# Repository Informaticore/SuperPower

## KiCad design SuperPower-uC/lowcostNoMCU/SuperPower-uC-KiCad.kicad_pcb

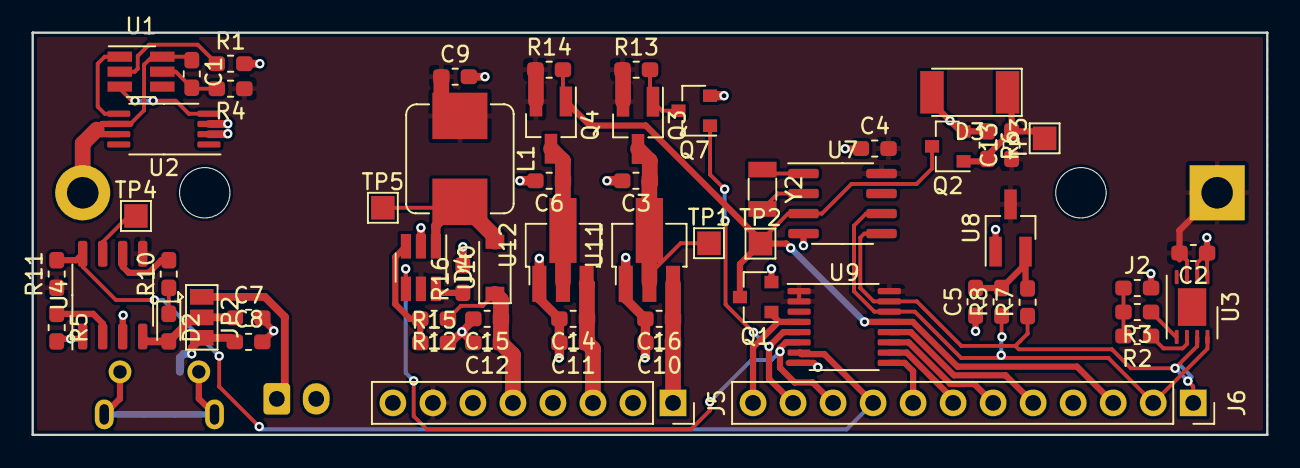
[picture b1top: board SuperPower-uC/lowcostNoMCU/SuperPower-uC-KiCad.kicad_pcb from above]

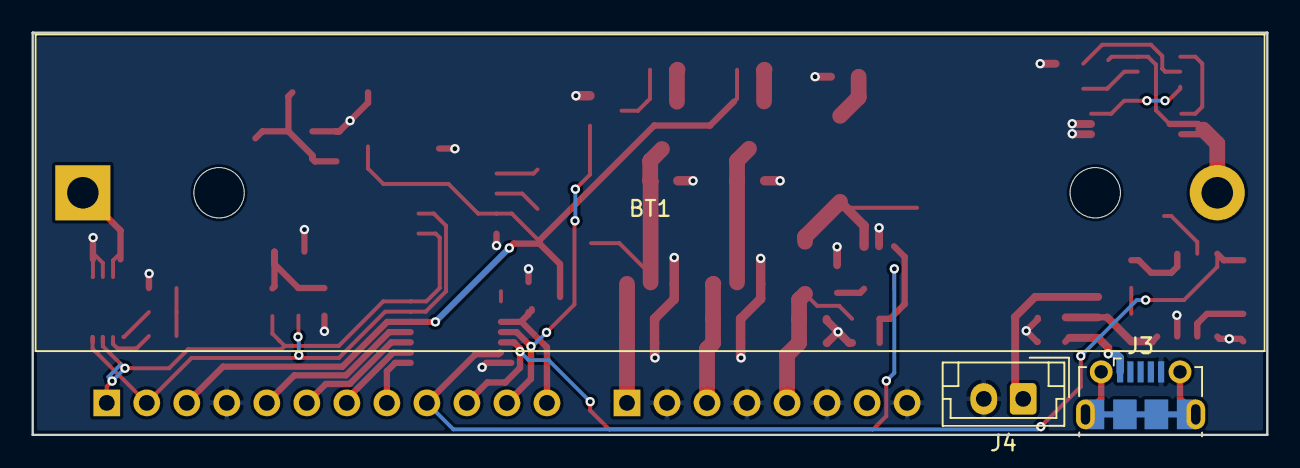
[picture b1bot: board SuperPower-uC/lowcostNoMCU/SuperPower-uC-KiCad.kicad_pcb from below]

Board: 2 copper layers, 78.4 x 25.5 mm, 63 parts (3 on the bottom side), 41 nets.

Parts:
BT1: Battery_Cell; BatteryHolder_MPD_BH-18650-PC2
C1, C2, C3, C4, C5, C6: 0.1µF; C_0603_1608Metric_Pad1.05x0.95mm_HandSolder
C7, C8, C9, C10, C11, C12: 1µF; C_0603_1608Metric_Pad1.05x0.95mm_HandSolder
C13, C14, C15, C16: 10µF; C_0603_1608Metric_Pad1.05x0.95mm_HandSolder
D2: LED; LED_0603_1608Metric_Pad1.05x0.95mm_HandSolder
D3: SM4007; D_MELF
D4: D_Schottky; D_SOD-123
J2: Thermistor; R_0603_1608Metric_Pad1.05x0.95mm_HandSolder
J3: USB_B_Micro; USB_Micro-B_Molex-105017-0001
J4: Solar in; JST_EH_B2B-EH-A_1x02_P2.50mm_Vertical
J5: Conn_01x08_Female; PinSocket_1x08_P2.54mm_Vertical
J6: Conn_01x12_Female; PinSocket_1x12_P2.54mm_Vertical
JP2: CHRG_Jumper; SolderJumper-3_P1.3mm_Open_Pad1.0x1.5mm
L1: 3.3u; L_Bourns_SRP7028A_7.3x6.6mm
Q1, Q2, Q7: 2N7002; SOT-23
Q3, Q4: AO3401A; SOT-23_Handsoldering
R1, R10: 1k; R_0603_1608Metric_Pad1.05x0.95mm_HandSolder
R2, R4: 100; R_0603_1608Metric_Pad1.05x0.95mm_HandSolder
R3, R7, R8: 10k; R_0603_1608Metric_Pad1.05x0.95mm_HandSolder
R5: 1.8k; R_0603_1608Metric_Pad1.05x0.95mm_HandSolder
R6: 1M; R_0603_1608Metric_Pad1.05x0.95mm_HandSolder
R11, R12, R13, R14: 180k; R_0603_1608Metric_Pad1.05x0.95mm_HandSolder
R15, R16: 22k; R_0603_1608Metric_Pad1.05x0.95mm_HandSolder
TP1, TP2, TP3, TP4, TP5: TestPoint; TestPoint_Pad_1.5x1.5mm
U1: FS312F-G; SOT-23-6_Handsoldering
U2: FS8205A; TSSOP-8_4.4x3mm_P0.65mm
U3: LC709203FQH; WDFN-8-1EP_4x3mm_P0.65mm_EP2.4x1.8mm
U4: TP4056; SOP-8_3.9x4.9mm_P1.27mm
U7: PCF8563T; SOIC-8_3.9x4.9mm_P1.27mm
U8: XC6206P332MR; SOT-23_Handsoldering
U9: TCA6408A; TSSOP-16_4.4x5mm_P0.65mm
U10: FP6291LR; SOT-23-6_Handsoldering
U11, U12: ME6210A33P; SOT-89-3_Handsoldering
Y2: 32.768KHz; Crystal_SMD_3215-2Pin_3.2x1.5mm

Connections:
/Battery Module/VBAT: BT1.1, C2.2, C4.2, C9.1, C13.1, J5.7, L1.1, Q3.2, Q4.2, R4.1, R11.1, R13.1, R14.1, U3.3, U4.5, U7.8, U8.3, U9.1, U9.2, U9.16, U10.5
/Charging Module/CHARGE-DISABLE: J6.9, R11.2, U4.8, U9.7
/Charging Module/INT: J6.3, Q1.3, Q2.3, Q4.1, R14.2, TP2.1, U7.3, U9.13
/Charging Module/SCL: J6.2, R8.1, U3.8, U7.6, U9.14
/Charging Module/SDA: J6.1, R7.1, U3.7, U7.5, U9.15
/Charging Module/STDBY: R10.2, U4.6
/Charging Module/VBUS: C8.1, J3.1, JP2.3
/Charging Module/VCHARGE: C7.1, D2.2, JP2.2, U4.4
/RTC and Cut-Off Module/3v3V_EN: J6.11, Q7.1, U9.5
/RTC and Cut-Off Module/3v3_MCU: C11.1, C14.1, J5.3, U12.3
/RTC and Cut-Off Module/5V_EN: J6.10, U9.6, U10.4
/RTC and Cut-Off Module/IO4: J6.8, U9.9
/RTC and Cut-Off Module/IO5: J6.7, U9.10
/RTC and Cut-Off Module/IO6: J6.6, U9.11
/RTC and Cut-Off Module/IO7: J6.5, U9.12
/RTC and Cut-Off Module/IO_INT: J6.12, Q1.1, U9.4
/RTC and Cut-Off Module/V_I2C: C5.2, R7.2, R8.2, U8.2
/Regulator Module/3v3: C10.1, C16.1, J5.1, U11.3
/Regulator Module/5V: C12.1, C15.1, D4.1, J5.5, R12.1
GND: C2.1, C3.2, C4.1, C5.1, C6.2, C7.2, C8.2, C9.2, C10.2, C11.2, C12.2, C14.2, C15.2, C16.2, D3.2, J2.2, J3.5, J4.2, J5.2, J5.4, J5.6, J5.8, J6.4, Q1.2, Q2.2, Q7.2, R1.2, R5.2, R6.1, R15.2, R16.2, U2.2, U2.3, U3.1, U3.2, U4.1, U4.3, U7.4, U8.1, U9.8, U10.2, U11.1, U12.1
unnamed: BT1.2, C1.2, U1.6, U2.6, U2.7
unnamed: C1.1, R4.2, U1.5
unnamed: C3.1, Q3.3, TP1.1, U11.2
unnamed: C6.1, Q4.3, U12.2
unnamed: C13.2, D3.1, Q2.1, R6.2, TP3.1
unnamed: D2.1, R10.1
unnamed: D4.2, L1.2, TP5.1, U10.1
unnamed: J2.1, R2.2, R3.2
unnamed: J4.1, JP2.1
unnamed: Q3.1, Q7.3, R13.2
unnamed: R1.1, U1.2
unnamed: R2.1, U3.6
unnamed: R3.1, U3.5
unnamed: R5.1, U4.2
unnamed: R12.2, R15.1, U10.3
unnamed: R16.1, U10.6
unnamed: TP4.1, U4.7
unnamed: U1.1, U2.5
unnamed: U1.3, U2.4
unnamed: U7.1, Y2.2
unnamed: U7.2, Y2.1

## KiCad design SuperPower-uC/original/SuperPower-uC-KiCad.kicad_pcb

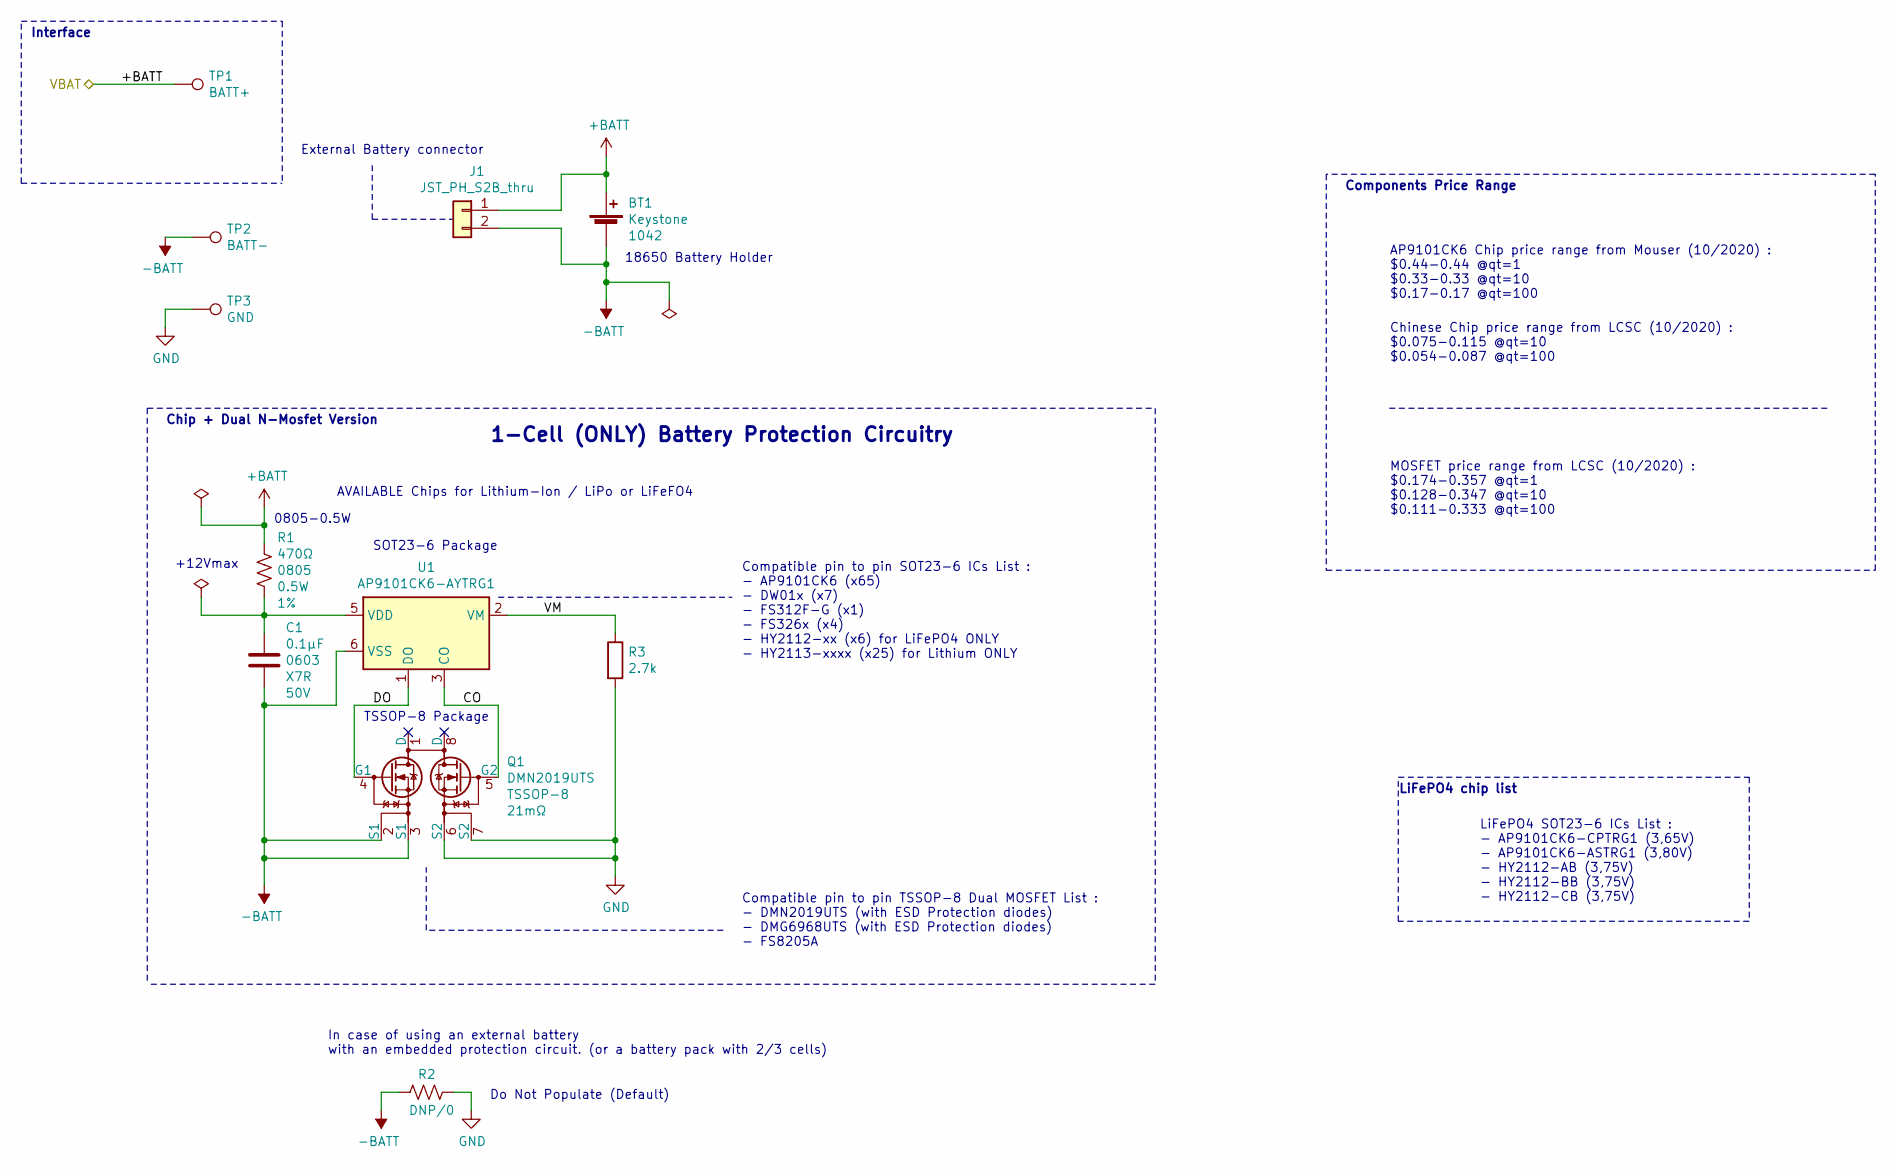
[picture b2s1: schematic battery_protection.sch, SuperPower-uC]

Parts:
BT1: Battery_Cell_Holder_18650_SMT_1042; BatteryHolder_Keystone_1042_1x18650; Farnell_ref ?
C1: CC0603JRX7R9BB104; C_0603_1608Metric; Farnell_ref 3369214
J1: JST_PH_S2B_thru; JST_PH_S2B-PH-K_1x02_P2.00mm_Horizontal; Farnell_ref 9491902
Q1: DMN2019UTS; TSSOP-8_4.4x3mm_P0.65mm; Farnell_check_date 2020-12-05
R1: ERJ-P06F4700V; R_0805_2012Metric; Farnell_check_date 2020-12-17
R2: DNP/0; R_0603_1608Metric
R3: 2.7k; R_0603_1608Metric
TP1: BATT+; TestPoint_Pad_D1.0mm
TP2: BATT-; TestPoint_Pad_D1.0mm
TP3: GND; TestPoint_Pad_D1.0mm
U1: AP9101CK6-AYTRG1; SOT-23-6; Farnell_check_date 2020-11-28

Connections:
+BATT: BT1.1 (+), J1.1, R1.1, TP1.1; also elsewhere on the board
-BATT: BT1.2 (-), C1.2, J1.2, Q1.2 (S1), Q1.3 (S1), R2.2, TP2.1, U1.6 (VSS)
/Battery Module/CO: Q1.5 (G2), U1.3 (CO)
/Battery Module/DO: Q1.4 (G1), U1.1 (DO)
/Battery Module/VM: R3.1, U1.2 (VM)
GND: Q1.6 (S2), Q1.7 (S2), R2.1, R3.2, TP3.1; also elsewhere on the board
unnamed: C1.1, R1.2, U1.5 (VDD)

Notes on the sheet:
SOT23-6 Package
TSSOP-8 Package
Compatible pin to pin SOT23-6 ICs List : - AP9101CK6 (x65) - DW01x (x7) - FS312F-G (x1) - FS326x (x4) - HY2112-xx (x6) for LiFePO4 ONLY - HY2113-xxxx (x25) for Lithium ONLY
AVAILABLE Chips for Lithium-Ion / LiPo or LiFeFO4
AP9101CK6 Chip price range from Mouser (10/2020) : $0.44-0.44 @qt=1 $0.33-0.33 @qt=10 $0.17-0.17 @qt=100
Compatible pin to pin TSSOP-8 Dual MOSFET List : - DMN2019UTS (with ESD Protection diodes) - DMG6968UTS (with ESD Protection diodes) - FS8205A
MOSFET price range from LCSC (10/2020) : $0.174-0.357 @qt=1 $0.128-0.347 @qt=10 $0.111-0.333 @qt=100
LiFePO4 SOT23-6 ICs List : - AP9101CK6-CPTRG1 (3,65V) - AP9101CK6-ASTRG1 (3,80V) - HY2112-AB (3,75V) - HY2112-BB (3,75V) - HY2112-CB (3,75V)
Chinese Chip price range from LCSC (10/2020) : $0.075-0.115 @qt=10 $0.054-0.087 @qt=100
Chip + Dual N-Mosfet Version
LiFePO4 chip list
In case of using an external battery with an embedded protection circuit. (or a battery pack with 2/3 cells)
External Battery connector
Interface
Components Price Range
18650 Battery Holder
1-Cell (ONLY) Battery Protection Circuitry
+12Vmax
Do Not Populate (Default)
0805-0.5W

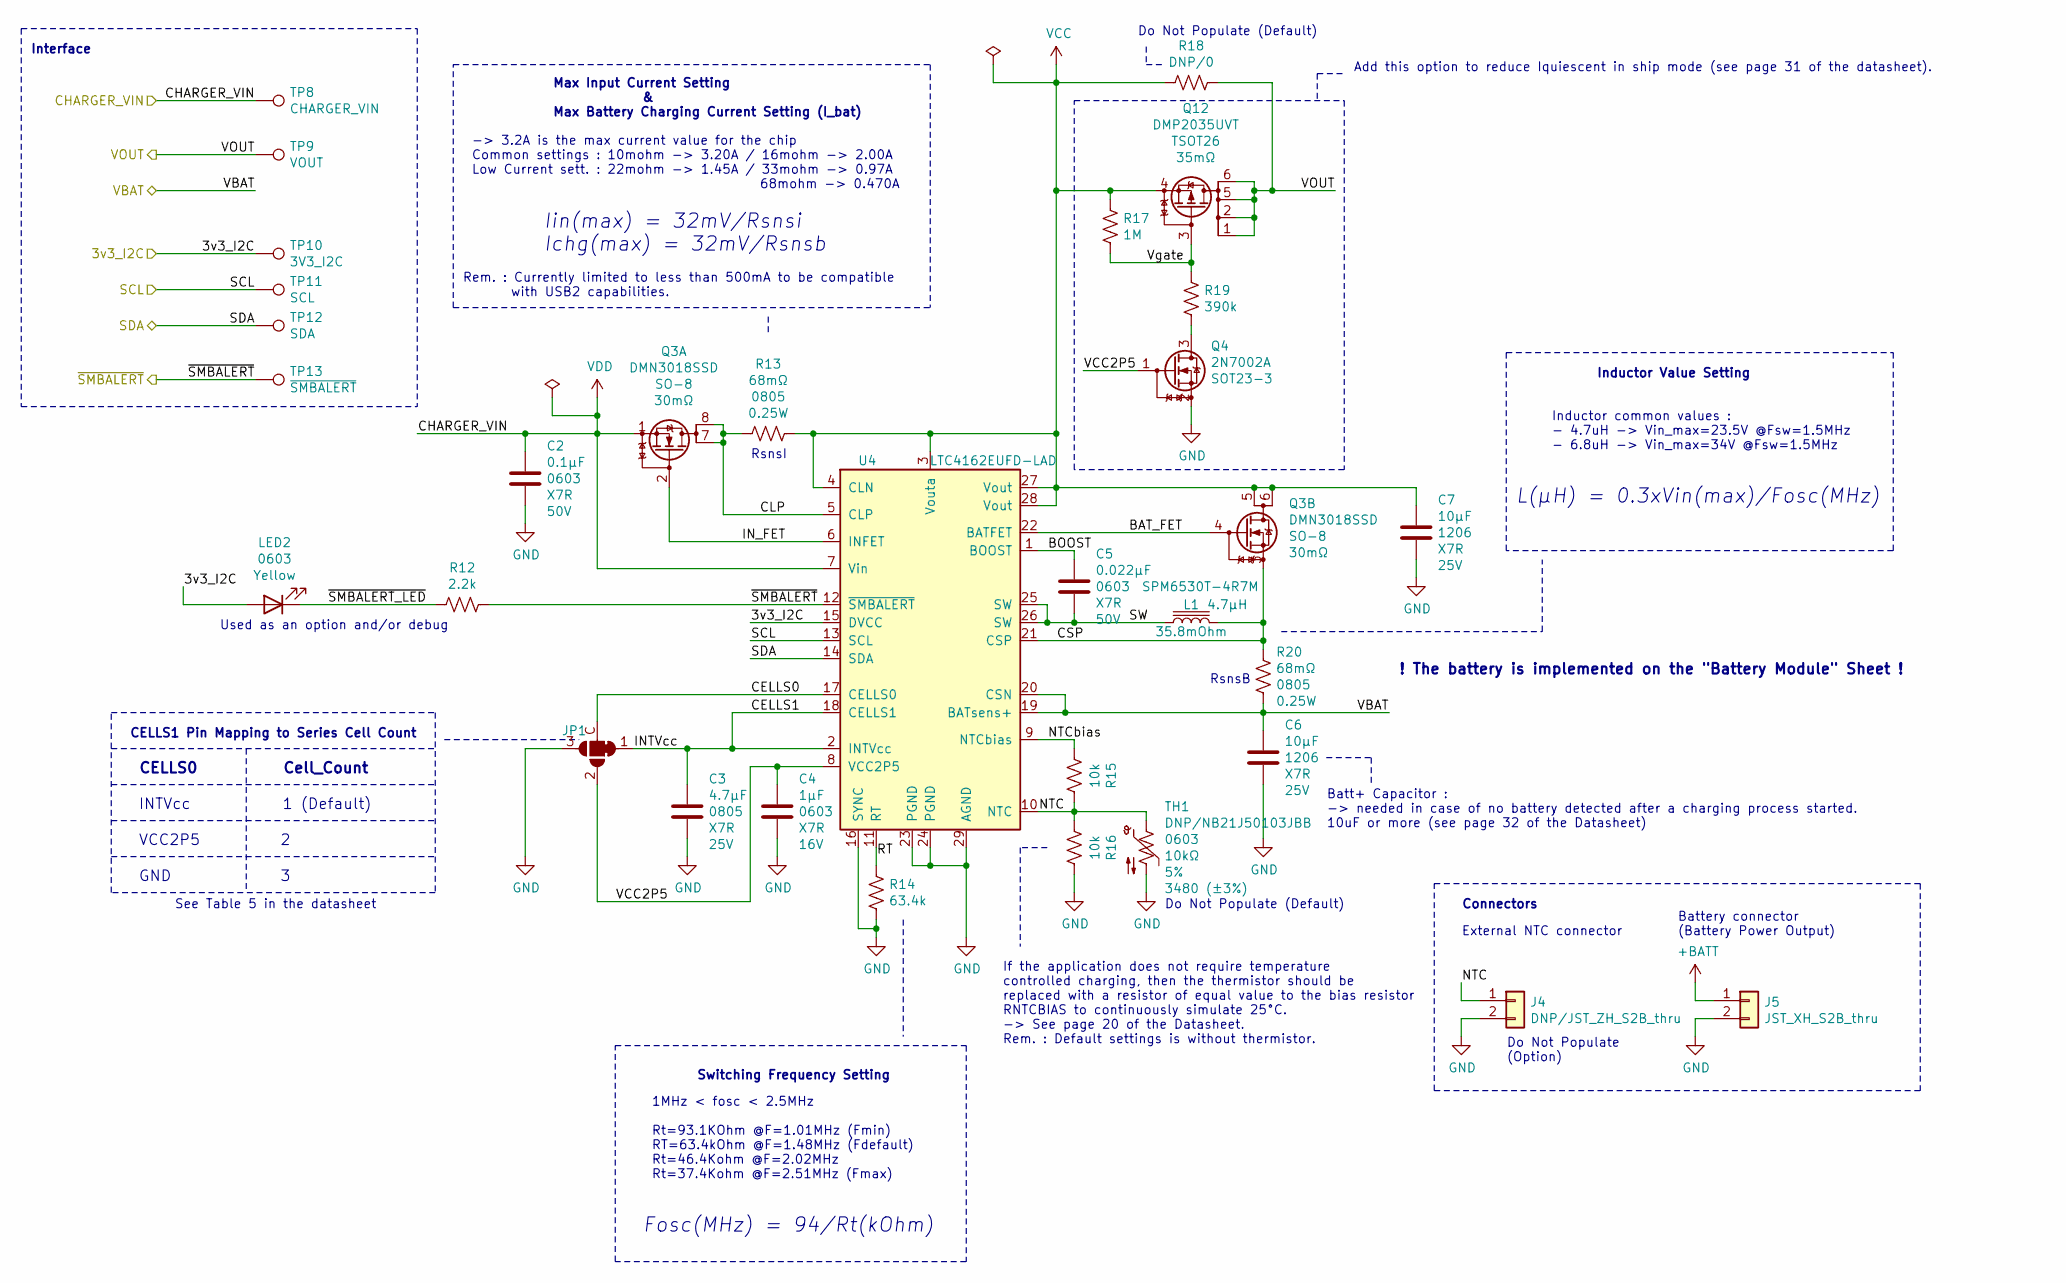
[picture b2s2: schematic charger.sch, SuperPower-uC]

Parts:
C2: CC0603JRX7R9BB104; C_0603_1608Metric; Farnell_ref 3369214
C3: TMK212AB7475KG-T; C_0805_2012Metric; Farnell_ref 2779199
C4: CL10B105KO8NNNC; C_0603_1608Metric; Farnell_ref 3013416
C5: CL10B223KB8NNNC; C_0603_1608Metric; Farnell_ref 3013425
C6, C7: CL31B106KAHNNNE; C_1206_3216Metric; Farnell_ref 3013526
J4: DNP/JST_ZH_S2B_thru; JST_ZH_S2B-ZR_1x02_P1.50mm_Horizontal; Farnell_ref 9491813
J5: JST_XH_S2B_thru; JST_XH_S2B-XH-A_1x02_P2.50mm_Horizontal; Farnell_ref 1516289
JP1: SolderJumper_4_Bridged_1C; SolderJumper-4_P2.0mm_Bridged1C_TrianglePad1.0x1.5mm_Number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
L1: SPM6530T-4R7M; L_TDK_SPM6530T; LCSC_ref C76857
LED2: 150060YS75000_0603; LED_0603_1608Metric; Farnell_ref 2322074
Q3: DMN3018SSD; SO-8_3.9x4.9mm_P1.27mm; Farnell_check_date 2020-12-05
Q4: 2N7002A; SOT-23; Farnell_ref 3127180
Q12: DMP2035UVT; SOT-23-6; Farnell_ref 3405183
R12: 2.2k; R_0603_1608Metric
R13, R20: RL0805FR-7W0R068L; R_0805_2012Metric; Farnell_ref 8067694
R14: 63.4k; R_0603_1608Metric
R15, R16: 10k; R_0603_1608Metric
R17: 1M; R_0603_1608Metric
R18: DNP/0; R_0603_1608Metric
R19: 390k; R_0603_1608Metric
TH1: DNP/NB21J50103JBB; R_0603_1608Metric; Farnell_ref 1672340
TP8: CHARGER_VIN; TestPoint_Pad_D1.0mm
TP9: VOUT; TestPoint_Pad_D1.0mm
TP10: 3V3_I2C; TestPoint_Pad_D1.0mm
TP11: SCL; TestPoint_Pad_D1.0mm
TP12: SDA; TestPoint_Pad_D1.0mm
TP13: ~SMBALERT; TestPoint_Pad_D1.0mm
U4: LTC4162EUFD-LAD; QFN-28-1EP_4x5mm_P0.5mm_EP2.65x3.65mm_ThermalVias; Farnell_check_date 2020-11-22

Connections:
+BATT: C6.1, J5.1, R20.1, U4.19 (BATsens+), U4.20 (CSN); also elsewhere on the board
/Charging Module/3v3_I2C: LED2.2 (A), TP10.1, U4.15 (DVCC); also elsewhere on the board
/Charging Module/BAT_FET: Q3.4 (G), U4.22 (BATFET)
/Charging Module/BOOST: C5.1, U4.1 (BOOST)
/Charging Module/CELLS0: JP1.C (Com), U4.17 (CELLS0)
/Charging Module/CELLS1: C3.1, JP1.1 (A), U4.2 (INTVcc), U4.18 (CELLS1)
/Charging Module/CLP: Q3.7 (D), Q3.8 (D), R13.2, U4.5 (CLP)
/Charging Module/CSP: L1.2, Q3.3 (S), R20.2, U4.21 (CSP)
/Charging Module/IN_FET: Q3.2 (G), U4.6 (INFET)
/Charging Module/NTC: J4.1, R15.1, R16.2, TH1.1, U4.10 (NTC)
/Charging Module/NTCbias: R15.2, U4.9 (NTCbias)
/Charging Module/RT: R14.2, U4.11 (RT)
/Charging Module/SW: C5.2, L1.1, U4.25 (SW), U4.26 (SW)
/Charging Module/VCC2P5: C4.1, JP1.2 (B), Q4.1 (G), U4.8 (VCC2P5)
/Charging Module/Vgate: Q12.3 (G), R17.2, R19.1
/Charging Module/~SMBALERT_LED: LED2.1 (K), R12.2
/Regulator and Cut-Off Module/VIN: Q12.1 (D), Q12.2 (D), Q12.5 (D), Q12.6 (D), R18.1, TP9.1; also elsewhere on the board
/SCL: TP11.1, U4.13 (SCL); also elsewhere on the board
/SDA: TP12.1, U4.14 (SDA); also elsewhere on the board
/~SMBALERT: R12.1, TP13.1, U4.12 (~SMBALERT); also elsewhere on the board
GND: C2.2, C3.2, C4.2, C6.2, C7.2, J4.2, J5.2, JP1.3 (C), Q4.2 (S), R14.1, R16.1, TH1.2, U4.16 (SYNC), U4.23 (PGND), U4.24 (PGND), U4.29 (AGND); also elsewhere on the board
unnamed: Q4.3 (D), R19.2
VCC: C7.1, Q3.5 (D), Q3.6 (D), Q12.4 (S), R13.1, R17.1, R18.2, U4.3 (Vouta), U4.4 (CLN), U4.27 (Vout), U4.28 (Vout)
VDD: C2.1, Q3.1 (S), TP8.1, U4.7 (Vin); also elsewhere on the board

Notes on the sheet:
RsnsB
RsnsI
If the application does not require temperature controlled charging, then the thermistor should be replaced with a resistor of equal value to the bias resistor RNTCBIAS to continuously simulate 25°C. -> See page 20 of the Datasheet. Rem. : Default settings is without thermistor.
Batt+ Capacitor : -> needed in case of no battery detected after a charging process started. 10uF or more (see page 32 of the Datasheet)
1MHz < fosc < 2.5MHz Rt=93.1KOhm @F=1.01MHz (Fmin) RT=63.4kOhm @F=1.48MHz (Fdefault) Rt=46.4Kohm @F=2.02MHz Rt=37.4Kohm @F=2.51MHz (Fmax)
Inductor common values : - 4.7uH -> Vin_max=23.5V @Fsw=1.5MHz - 6.8uH -> Vin_max=34V @Fsw=1.5MHz
Add this option to reduce Iquiescent in ship mode (see page 31 of the datasheet).
External NTC connector
Switching Frequency Setting
Max Input Current Setting & Max Battery Charging Current Setting (I_bat)
-> 3.2A is the max current value for the chip Common settings : 10mohm -> 3.20A / 16mohm -> 2.00A Low Current sett. : 22mohm -> 1.45A / 33mohm -> 0.97A 68mohm -> 0.470A
Inductor Value Setting
Battery connector (Battery Power Output)
Used as an option and/or debug
See Table 5 in the datasheet
Connectors
! The battery is implemented on the "Battery Module" Sheet !
Iin(max) = 32mV/Rsnsi Ichg(max) = 32mV/Rsnsb
Fosc(MHz) = 94/Rt(kOhm)
L(µH) = 0.3xVin(max)/Fosc(MHz)
CELLS1 Pin Mapping to Series Cell Count
CELLS0
Cell_Count
INTVcc
VCC2P5
GND
1 (Default)
Rem. : Currently limited to less than 500mA to be compatible with USB2 capabilities.
Interface
Do Not Populate (Option)
Do Not Populate (Default)

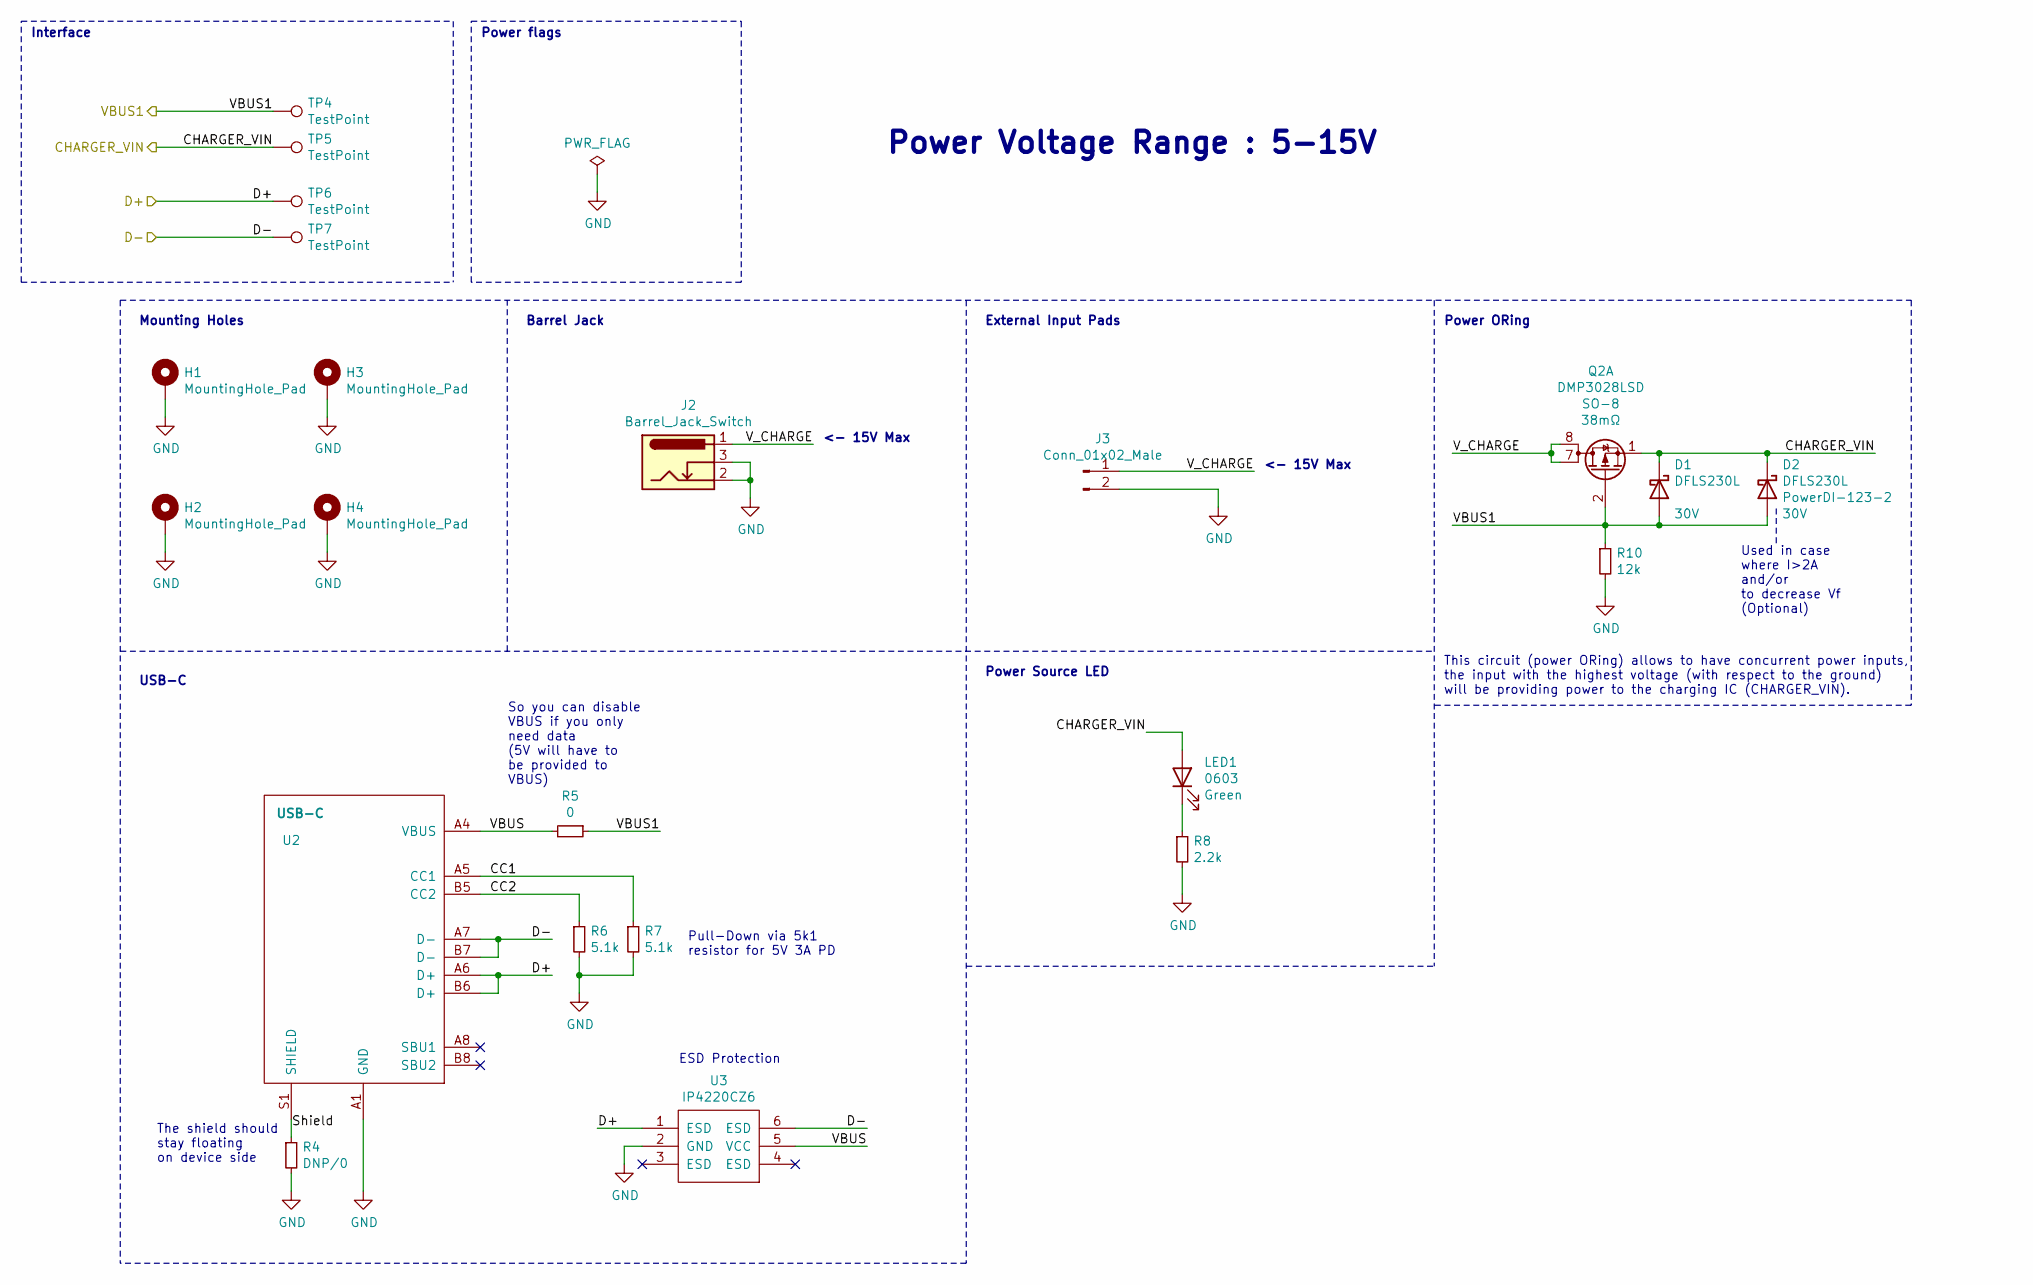
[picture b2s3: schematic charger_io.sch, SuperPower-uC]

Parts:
D1, D2: DFLS230L; D_PowerDI-123; Farnell_ref 1858663
H1, H3: MountingHole_Pad; MountingHole_2.7mm_M2.5_Pad_Via
H2, H4: MountingHole_Pad; MountingHole_2.7mm_Pad_Via
J2: Barrel_Jack_Switch; BarrelJack_Wuerth_6941xx301002
J3: Conn_01x02_Male; ext_input_pads
LED1: 150060VS75000_0603; LED_0603_1608Metric; Farnell_ref 2322073
Q2: DMP3028LSD; SO-8_3.9x4.9mm_P1.27mm; Farnell_check_date 2020-12-05
R4: DNP/0; R_0603_1608Metric
R5: 0; R_0603_1608Metric
R6, R7: 5.1k; R_0603_1608Metric
R8: 2.2k; R_0603_1608Metric
R10: 12k; R_0603_1608Metric
TP4, TP5, TP6, TP7: TestPoint; TestPoint_Pad_D1.0mm
U2: USB-C; usb-c-usb4110
U3: IP4220CZ6; TSOP-6_1.65x3.05mm_P0.95mm

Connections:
/Charger inputs and USB IO/CC1: R7.1, U2.A5 (CC1)
/Charger inputs and USB IO/CC2: R6.1, U2.B5 (CC2)
/Charger inputs and USB IO/Shield: R4.1, U2.S1 (SHIELD)
/Charger inputs and USB IO/V_CHARGE: J2.1, J3.1, Q2.7 (D), Q2.8 (D)
/D+: TP6.1, U2.A6 (D+), U2.B6 (D+), U3.1 (ESD); also elsewhere on the board
/D-: TP7.1, U2.A7 (D-), U2.B7 (D-), U3.6 (ESD); also elsewhere on the board
/VBUS1: D1.2 (A), D2.2 (A), Q2.2 (G), R5.1, R10.1, TP4.1; also elsewhere on the board
GND: H1.1, H2.1, H3.1, H4.1, J2.2, J2.3, J3.2, R4.2, R6.2, R7.2, R8.2, R10.2, U2.A1 (GND), U2.A12 (GND), U2.B1 (GND), U2.B12 (GND), U3.2 (GND); also elsewhere on the board
unnamed: LED1.1 (K), R8.1
VBUS: R5.2, U2.A4 (VBUS), U2.A9 (VBUS), U2.B4 (VBUS), U2.B9 (VBUS), U3.5 (VCC)
VDD: D1.1 (K), D2.1 (K), LED1.2 (A), Q2.1 (S), TP5.1; also elsewhere on the board

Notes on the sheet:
Pull-Down via 5k1 resistor for 5V 3A PD
Barrel Jack
External Input Pads
USB-C
So you can disable VBUS if you only need data (5V will have to be provided to VBUS)
ESD Protection
The shield should stay floating on device side
Power ORing
This circuit (power ORing) allows to have concurrent power inputs, the input with the highest voltage (with respect to the ground) will be providing power to the charging IC (CHARGER_VIN).
Power Source LED
Interface
Power Voltage Range : 5-15V
<- 15V Max
Mounting Holes
Power flags
Used in case where I>2A and/or to decrease Vf (Optional)

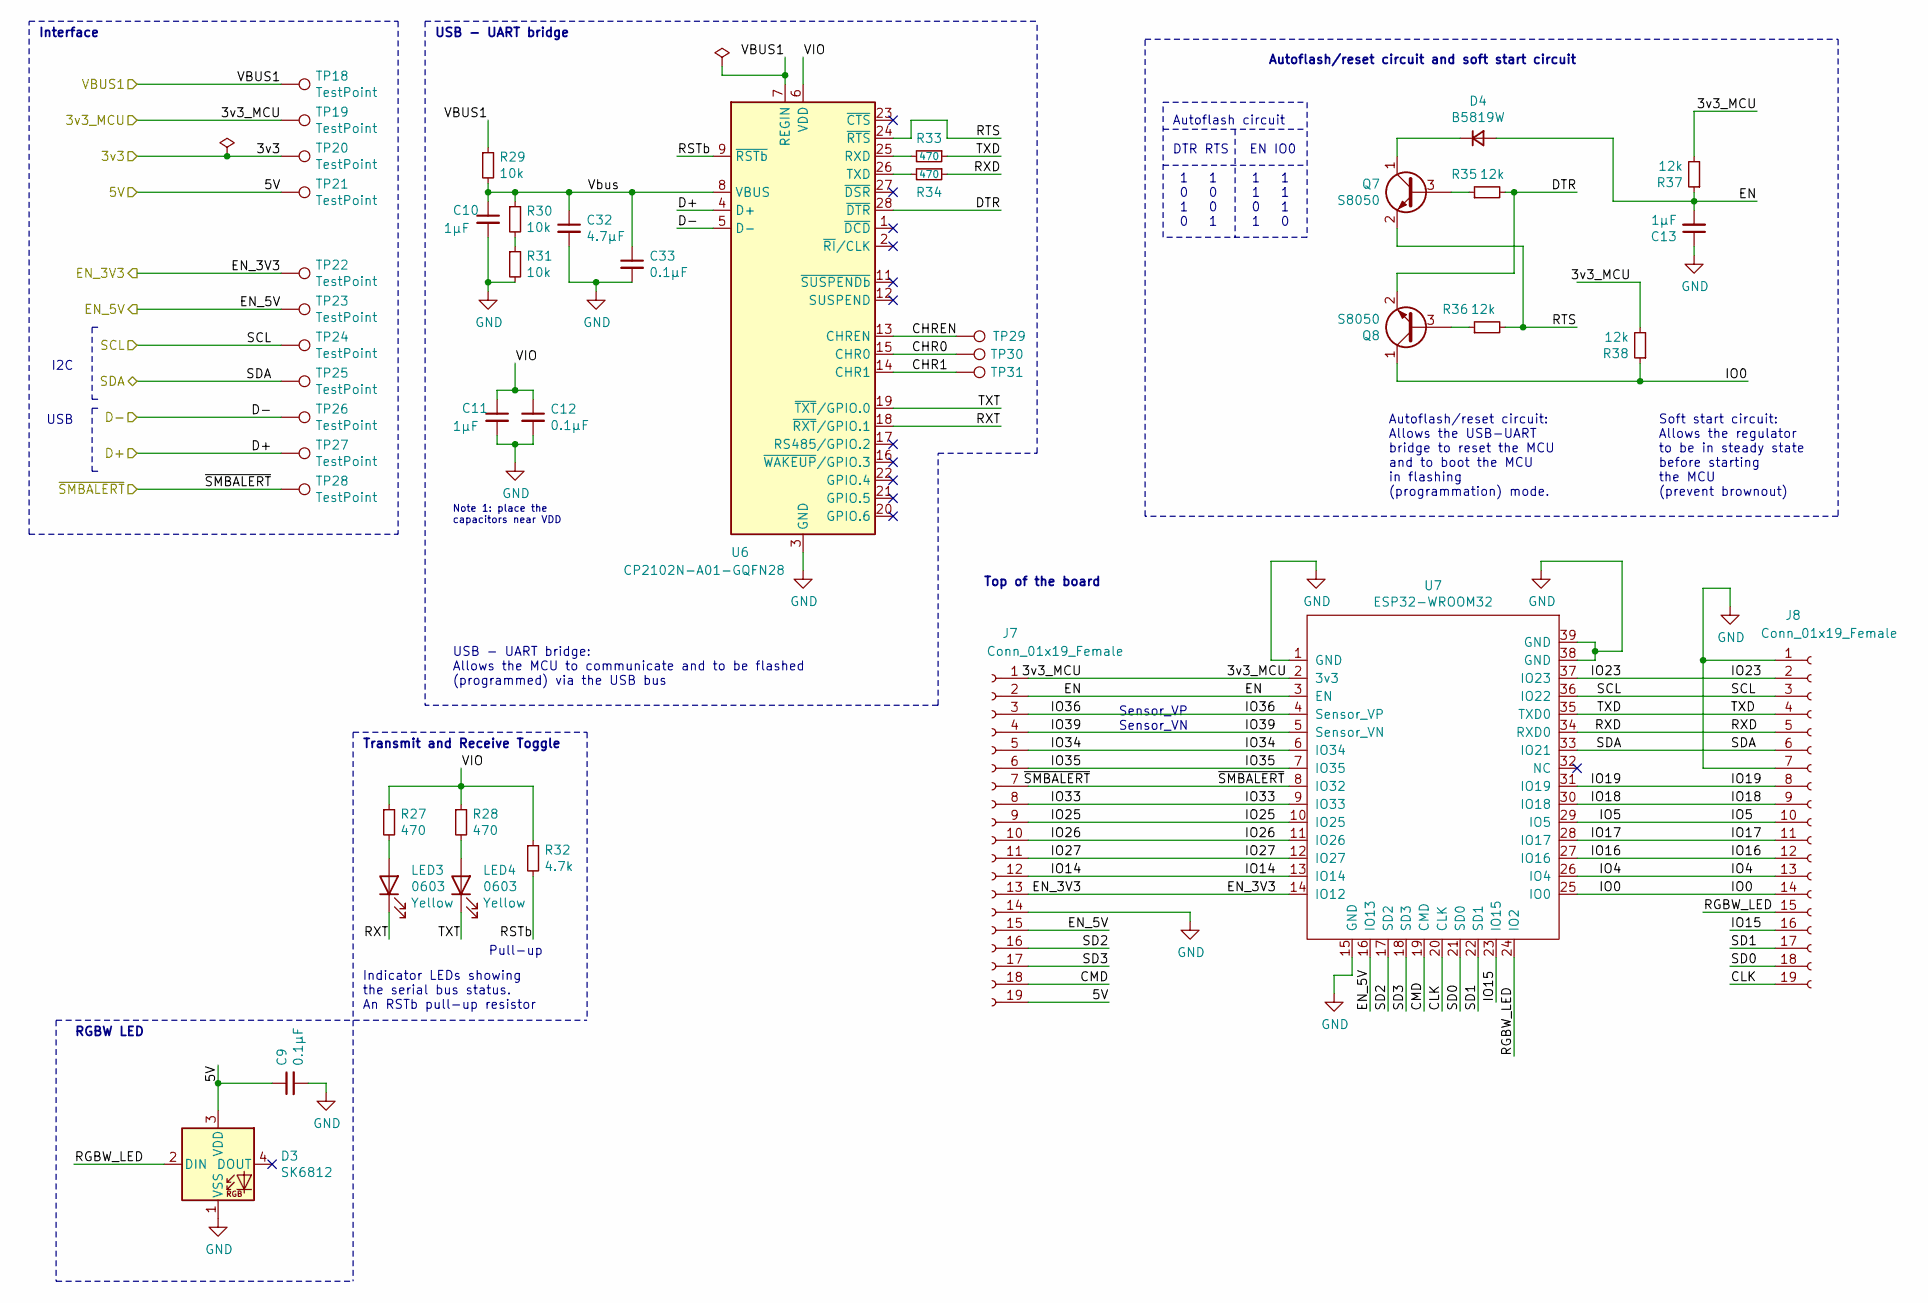
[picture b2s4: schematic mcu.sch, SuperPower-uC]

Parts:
C9, C12, C33: 0.1µF; C_0603_1608Metric
C10, C11, C13: 1µF; C_0603_1608Metric
C32: 4.7µF; C_0603_1608Metric
D3: SK6812; LED_SK6812_PLCC4_5.0x5.0mm_P3.2mm
D4: B5819W; D_SOD-123
J7, J8: Conn_01x19_Female; PinSocket_1x19_P2.54mm_Vertical
LED3, LED4: 150060YS75000_0603; LED_0603_1608Metric; Farnell_ref 2322074
Q7, Q8: S8050; SOT-23
R27, R28, R33, R34: 470; R_0603_1608Metric
R29, R30, R31: 10k; R_0603_1608Metric
R32: 4.7k; R_0603_1608Metric
R35, R36, R37, R38: 12k; R_0603_1608Metric
TP18, TP19, TP20, TP21, TP22, TP23, TP24, TP25, TP26, TP27, TP28, TP29, TP30, TP31: TestPoint; TestPoint_Pad_D1.0mm
U6: CP2102N-A01-GQFN28; QFN-28-1EP_5x5mm_P0.5mm_EP3.35x3.35mm
U7: ESP32-WROOM32; ESP32-WROOM-32; LCSC C82899

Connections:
/D+: TP27.1, U6.4 (D+); also elsewhere on the board
/D-: TP26.1, U6.5 (D-); also elsewhere on the board
/MCU Module/3v3: TP20.1; also elsewhere on the board
/MCU Module/3v3_MCU: J7.1, R37.2, R38.2, TP19.1, U7.2 (3v3); also elsewhere on the board
/MCU Module/5V: C9.1, D3.3 (VDD), J7.19, TP21.1; also elsewhere on the board
/MCU Module/CHR0: TP30.1, U6.15 (CHR0)
/MCU Module/CHR1: TP31.1, U6.14 (CHR1)
/MCU Module/CHREN: TP29.1, U6.13 (CHREN)
/MCU Module/CLK: J8.19, U7.20 (CLK)
/MCU Module/CMD: J7.18, U7.19 (CMD)
/MCU Module/DTR: Q8.2 (E), R35.2, U6.28 (~DTR)
/MCU Module/EN: C13.2, D4.2 (A), J7.2, R37.1, U7.3 (EN)
/MCU Module/EN_3V3: J7.13, TP22.1, U7.14 (IO12); also elsewhere on the board
/MCU Module/EN_5V: J7.15, TP23.1, U7.16 (IO13); also elsewhere on the board
/MCU Module/IO0: J8.14, Q8.1 (C), R38.1, U7.25 (IO0)
/MCU Module/IO4: J8.13, U7.26 (IO4)
/MCU Module/IO5: J8.10, U7.29 (IO5)
/MCU Module/IO14: J7.12, U7.13 (IO14)
/MCU Module/IO15: J8.16, U7.23 (IO15)
/MCU Module/IO16: J8.12, U7.27 (IO16)
/MCU Module/IO17: J8.11, U7.28 (IO17)
/MCU Module/IO18: J8.9, U7.30 (IO18)
/MCU Module/IO19: J8.8, U7.31 (IO19)
/MCU Module/IO23: J8.2, U7.37 (IO23)
/MCU Module/IO25: J7.9, U7.10 (IO25)
/MCU Module/IO26: J7.10, U7.11 (IO26)
/MCU Module/IO27: J7.11, U7.12 (IO27)
/MCU Module/IO33: J7.8, U7.9 (IO33)
/MCU Module/IO34: J7.5, U7.6 (IO34)
/MCU Module/IO35: J7.6, U7.7 (IO35)
/MCU Module/IO36: J7.3, U7.4 (Sensor_VP)
/MCU Module/IO39: J7.4, U7.5 (Sensor_VN)
/MCU Module/RGBW_LED: D3.2 (DIN), J8.15, U7.24 (IO2)
/MCU Module/RSTb: R32.2, U6.9 (~RSTb)
/MCU Module/RTS: Q7.2 (E), R36.2, U6.24 (~RTS)
/MCU Module/RXD: J8.5, R34.1, U7.34 (RXD0)
/MCU Module/RXT: LED3.1 (K), U6.18 (~RXT~/GPIO.1)
/MCU Module/SD0: J8.18, U7.21 (SD0)
/MCU Module/SD1: J8.17, U7.22 (SD1)
/MCU Module/SD2: J7.16, U7.17 (SD2)
/MCU Module/SD3: J7.17, U7.18 (SD3)
/MCU Module/TXD: J8.4, R33.1, U7.35 (TXD0)
/MCU Module/TXT: LED4.1 (K), U6.19 (~TXT~/GPIO.0)
/MCU Module/VIO: C11.1, C12.1, R27.1, R28.1, R32.1, U6.6 (VDD)
/MCU Module/Vbus: C10.1, C32.1, C33.1, R29.2, R30.1, U6.8 (VBUS)
/SCL: J8.3, TP24.1, U7.36 (IO22); also elsewhere on the board
/SDA: J8.6, TP25.1, U7.33 (IO21); also elsewhere on the board
/VBUS1: R29.1, TP18.1, U6.7 (REGIN); also elsewhere on the board
/~SMBALERT: J7.7, TP28.1, U7.8 (IO32); also elsewhere on the board
GND: C9.2, C10.2, C11.2, C12.2, C13.1, C32.2, C33.2, D3.1 (VSS), J7.14, J8.1, J8.7, R31.2, U6.3 (GND), U6.29 (GND), U7.1 (GND), U7.15 (GND), U7.38 (GND), U7.39 (GND); also elsewhere on the board
unnamed: D4.1 (K), Q7.1 (C)
unnamed: LED3.2 (A), R27.2
unnamed: LED4.2 (A), R28.2
unnamed: Q7.3 (B), R35.1
unnamed: Q8.3 (B), R36.1
unnamed: R30.2, R31.1
unnamed: R33.2, U6.25 (RXD)
unnamed: R34.2, U6.26 (TXD)

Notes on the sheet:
USB - UART bridge
Autoflash circuit DTR RTS EN IO0 1 1 1 1 0 0 1 1 1 0 0 1 0 1 1 0
Autoflash/reset circuit and soft start circuit
Transmit and Receive Toggle
Interface
Pull-up
Note 1: place the capacitors near VDD
Top of the board
Sensor_VP Sensor_VN
Indicator LEDs showing the serial bus status. An RSTb pull-up resistor
Soft start circuit: Allows the regulator to be in steady state before starting the MCU (prevent brownout)
USB - UART bridge: Allows the MCU to communicate and to be flashed (programmed) via the USB bus
I2C
USB
RGBW LED
Autoflash/reset circuit: Allows the USB-UART bridge to reset the MCU and to boot the MCU in flashing (programmation) mode.

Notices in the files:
SuperPower-uC/lowcostNoMCU/battery_protection.sch:
Licence: CERN-OHL-W
